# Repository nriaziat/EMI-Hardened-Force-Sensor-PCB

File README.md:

# EMI Hardened Force Sensor PCB

<!--- This template should be used if the project contains hardware designs. If the project contains both hardware and software designs, please also refer to software-readme-template.md and incorporate relevant sections. -->

## Contents

<!---List file contents of the project, in table.--->

| File/folder | Description |
|-------------|-------------|
| `MazeStrainGaugeAmplifier.pdf`       | Schematic |
| `ibom.html`       | Bill of materials |
| `PCB.pdf`        | Report on PCB stack-up |
| `README.md` | This README file. |
| `LICENSE`   | The license for the project. |

## Design Tools

* KiCAD 6.0

## Key concepts

For more information about this project, please refer to our publication: [Riaziat, Naveed D., et al. "Investigating Haptic Feedback in Vision-Deficient Millirobot Telemanipulation." IEEE Robotics and Automation Letters (2024)](https://ieeexplore.ieee.org/abstract/document/10521760/).
Designed for use with the Texas Measurment [QMFLA-5-350-11-1LJAY-F](https://tml.jp/e/product/strain_gauge/mf_list.html) and the [RP2040](https://www.raspberrypi.com/products/rp2040/).
For maximum EMI resistance, we reccommend using twisted and shielded cabling as well as the included 3D printed housing with copper tape lining. 

## Project expectations

* The design has been manufactured and tested. Board was ordered through OSH Park and hand assembled.

### Expected support for the project

<!---If you will reply to issues, please suggest how users should report problems or reach out. Github issues is preferable.--->

* Will attempt reply to Github Issues with no guarantee.
* Project is provided without any support. 

## License

For details on license, see LICENSE in this directory.

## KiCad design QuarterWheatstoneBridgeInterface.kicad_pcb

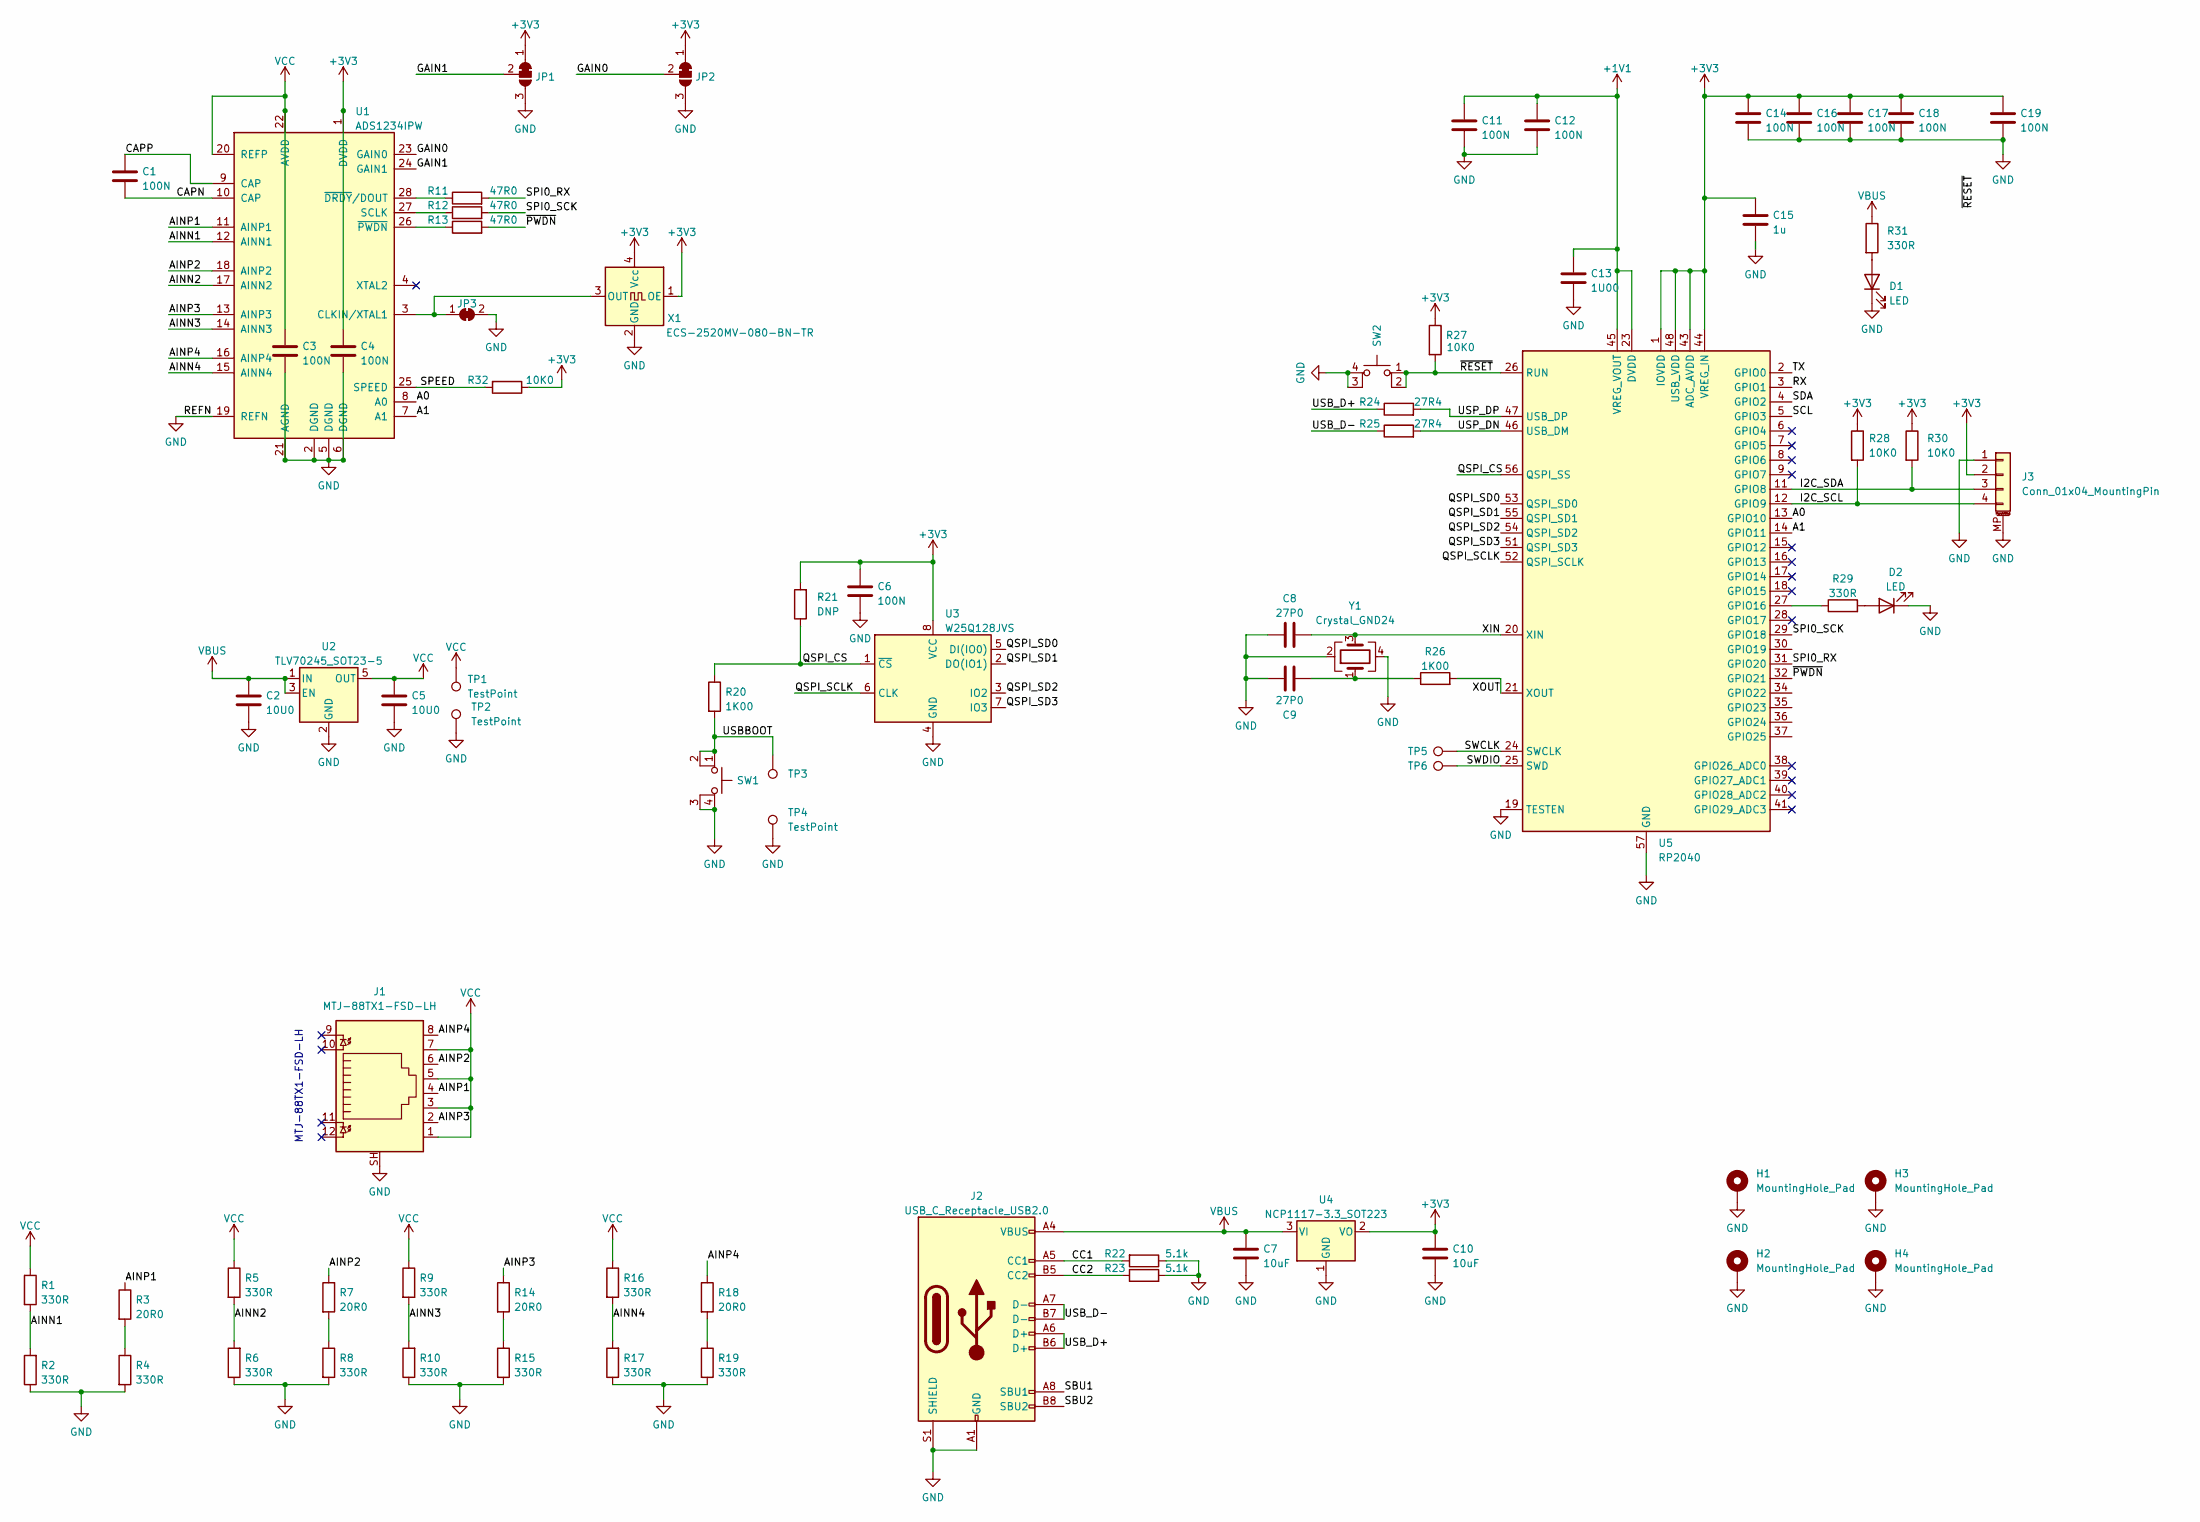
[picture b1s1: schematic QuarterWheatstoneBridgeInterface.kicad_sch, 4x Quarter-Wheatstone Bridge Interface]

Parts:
C1, C3, C4, C6, C11, C12, C14, C16, C17, C18, C19: 100N; C_0402_1005Metric_Pad0.74x0.62mm_HandSolder
C2, C5: 10U0; C_0402_1005Metric_Pad0.74x0.62mm_HandSolder
C7, C10: 10uF; C_0402_1005Metric_Pad0.74x0.62mm_HandSolder
C8, C9: 27P0; C_0402_1005Metric_Pad0.74x0.62mm_HandSolder
C13: 1U00; C_0402_1005Metric_Pad0.74x0.62mm_HandSolder
C15: 1u; C_0402_1005Metric_Pad0.74x0.62mm_HandSolder
D1, D2: LED; LED_0603_1608Metric_Pad1.05x0.95mm_HandSolder
H1, H2, H3, H4: MountingHole_Pad; MountingHole_2.2mm_M2_DIN965_Pad
J1: MTJ-88TX1-FSD-LH; RJ45_Hanrun_HR911105A
J2: USB_C_Receptacle_USB2.0; USB_C_Receptacle_HRO_TYPE-C-31-M-12
J3: Conn_01x04_MountingPin; JST_SH_BM04B-SRSS-TB_1x04-1MP_P1.00mm_Vertical
JP1, JP2: SolderJumper_3_Bridged12; SolderJumper-3_P1.3mm_Bridged12_Pad1.0x1.5mm
JP3: SolderJumper_2_Bridged; SolderJumper-2_P1.3mm_Bridged_Pad1.0x1.5mm
R1, R2, R4, R5, R6, R8, R9, R10, R15, R16, R17, R19, R29, R31: 330R; R_0402_1005Metric_Pad0.72x0.64mm_HandSolder
R3, R7, R14, R18: 20R0; R_0402_1005Metric_Pad0.72x0.64mm_HandSolder
R11, R12, R13: 47R0; R_0402_1005Metric_Pad0.72x0.64mm_HandSolder
R20, R26: 1K00; R_0402_1005Metric_Pad0.72x0.64mm_HandSolder
R21: DNP; R_0402_1005Metric_Pad0.72x0.64mm_HandSolder
R22, R23: 5.1k; R_0402_1005Metric_Pad0.72x0.64mm_HandSolder
R24, R25: 27R4; R_0402_1005Metric_Pad0.72x0.64mm_HandSolder
R27, R28, R30, R32: 10K0; R_0402_1005Metric_Pad0.72x0.64mm_HandSolder
SW1, SW2: SW_MEC_5E; SW_TH_Tactile_Omron_B3F-10xx
TP1, TP2, TP4: TestPoint; TestPoint_Pad_D3.0mm
TP3, TP5, TP6: TestPoint; TestPoint_Pad_D4.0mm
U1: ADS1234IPW; TSSOP-28_4.4x9.7mm_P0.65mm
U2: TLV70245_SOT23-5; SOT-23-5
U3: W25Q128JVS; SOIC-8_5.23x5.23mm_P1.27mm
U4: NCP1117-3.3_SOT223; SOT-223-3_TabPin2
U5: RP2040; QFN-56-1EP_7x7mm_P0.4mm_EP3.2x3.2mm
X1: ECS-2520MV-080-BN-TR; Oscillator_SMD_SeikoEpson_SG210-4Pin_2.5x2.0mm
Y1: Crystal_GND24; Crystal_SMD_3225-4Pin_3.2x2.5mm_HandSoldering

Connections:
+1V1: C11.1, C12.1, C13.1, U5.23 (DVDD), U5.45 (VREG_VOUT), U5.50 (DVDD)
+3V3: C4.1, C6.1, C10.1, C14.1, C15.1, C16.1, C17.1, C18.1, C19.1, J3.2, JP1.1 (A), JP2.1 (A), R21.2, R27.1, R28.1, R30.1, R32.1, U1.1 (DVDD), U3.8 (VCC), U4.2 (VO), U5.1 (IOVDD), U5.10 (IOVDD), U5.22 (IOVDD), U5.33 (IOVDD), U5.42 (IOVDD), U5.43 (ADC_AVDD), U5.44 (VREG_IN), U5.48 (USB_VDD), U5.49 (IOVDD), X1.1 (OE), X1.4 (Vcc)
/A0: U1.8 (A0), U5.13 (GPIO10)
/A1: U1.7 (A1), U5.14 (GPIO11)
/AINN1: R1.2, R2.2, U1.12 (AINN1)
/AINN2: R5.2, R6.2, U1.17 (AINN2)
/AINN3: R9.2, R10.2, U1.14 (AINN3)
/AINN4: R16.2, R17.2, U1.15 (AINN4)
/AINP1: J1.4, R3.1, U1.11 (AINP1)
/AINP2: J1.6, R7.1, U1.18 (AINP2)
/AINP3: J1.2, R14.1, U1.13 (AINP3)
/AINP4: J1.8, R18.1, U1.16 (AINP4)
/CAPN: C1.2, U1.10 (CAP)
/CAPP: C1.1, U1.9 (CAP)
/CC1: J2.A5 (CC1), R22.2
/CC2: J2.B5 (CC2), R23.1
/GAIN0: JP2.2 (C), U1.23 (GAIN0)
/GAIN1: JP1.2 (C), U1.24 (GAIN1)
/I2C_SCL: J3.4, R28.2, U5.12 (GPIO9)
/I2C_SDA: J3.3, R30.2, U5.11 (GPIO8)
/QSPI_CS: R20.1, R21.1, U3.1 (~CS), U5.56 (QSPI_SS)
/QSPI_SCLK: U3.6 (CLK), U5.52 (QSPI_SCLK)
/QSPI_SD0: U3.5 (DI(IO0)), U5.53 (QSPI_SD0)
/QSPI_SD1: U3.2 (DO(IO1)), U5.55 (QSPI_SD1)
/QSPI_SD2: U3.3 (IO2), U5.54 (QSPI_SD2)
/QSPI_SD3: U3.7 (IO3), U5.51 (QSPI_SD3)
/RX: U5.3 (GPIO1)
/SBU1: J2.A8 (SBU1)
/SBU2: J2.B8 (SBU2)
/SCL: U5.5 (GPIO3)
/SDA: U5.4 (GPIO2)
/SPEED: R32.2, U1.25 (SPEED)
/SPI0_RX: R11.2, U5.31 (GPIO20)
/SPI0_SCK: R12.2, U5.29 (GPIO18)
/SWCLK: TP5.1, U5.24 (SWCLK)
/SWDIO: TP6.1, U5.25 (SWD)
/TX: U5.2 (GPIO0)
/USBBOOT: R20.2, SW1.1, SW1.2, TP3.1
/USB_D+: J2.A6 (D+), J2.B6 (D+), R24.1
/USB_D-: J2.A7 (D-), J2.B7 (D-), R25.1
/USP_DN: R25.2, U5.46 (USB_DM)
/USP_DP: R24.2, U5.47 (USB_DP)
/XIN: C8.2, U5.20 (XIN), Y1.3
/XOUT: R26.2, U5.21 (XOUT)
/~PWDN: R13.2, U5.32 (GPIO21)
/~RESET: R27.2, SW2.1, SW2.2, U5.26 (RUN)
GND: C2.2, C3.2, C4.2, C5.2, C6.2, C7.2, C8.1, C9.2, C10.2, C11.2, C12.2, C13.2, C14.2, C15.2, C16.2, C17.2, C18.2, C19.2, D1.1 (K), D2.1 (K), H1.1, H2.1, H3.1, H4.1, J1.SH, J2.A1 (GND), J2.A12 (GND), J2.B1 (GND), J2.B12 (GND), J2.S1 (SHIELD), J3.1, J3.MP (MountPin), JP1.3 (B), JP2.3 (B), JP3.2 (B), R2.1, R4.2, R6.1, R8.2, R10.1, R15.2, R17.1, R19.2, R22.1, R23.2, SW1.3 (K), SW1.4 (A), SW2.3 (K), SW2.4 (A), TP2.1, TP4.1, U1.2 (DGND), U1.5 (DGND), U1.6 (DGND), U1.19 (REFN), U1.21 (AGND), U2.2 (GND), U3.4 (GND), U4.1 (GND), U5.19 (TESTEN), U5.57 (GND), X1.2 (GND), Y1.2, Y1.4
unnamed: C9.1, R26.1, Y1.1
unnamed: D1.2 (A), R31.2
unnamed: D2.2 (A), R29.2
unnamed: JP3.1 (A), U1.3 (CLKIN/XTAL1), X1.3 (OUT)
unnamed: R3.2, R4.1
unnamed: R7.2, R8.1
unnamed: R11.1, U1.28 (~DRDY/DOUT)
unnamed: R12.1, U1.27 (SCLK)
unnamed: R13.1, U1.26 (~PWDN)
unnamed: R14.2, R15.1
unnamed: R18.2, R19.1
unnamed: R29.1, U5.27 (GPIO16)
VBUS: C2.1, C7.1, J2.A4 (VBUS), J2.A9 (VBUS), J2.B4 (VBUS), J2.B9 (VBUS), R31.1, U2.1 (IN), U2.3 (EN), U4.3 (VI)
VCC: C3.1, C5.1, J1.1, J1.3, J1.5, J1.7, R1.1, R5.1, R9.1, R16.1, TP1.1, U1.20 (REFP), U1.22 (AVDD), U2.5 (OUT)

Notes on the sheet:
MTJ-88TX1-FSD-LH

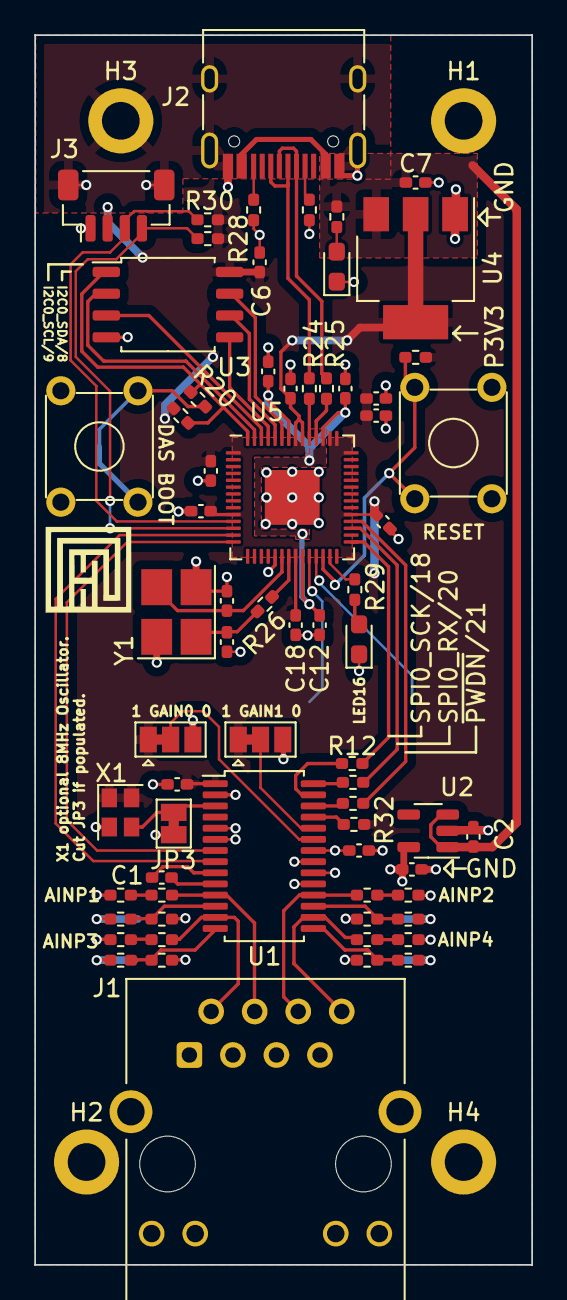
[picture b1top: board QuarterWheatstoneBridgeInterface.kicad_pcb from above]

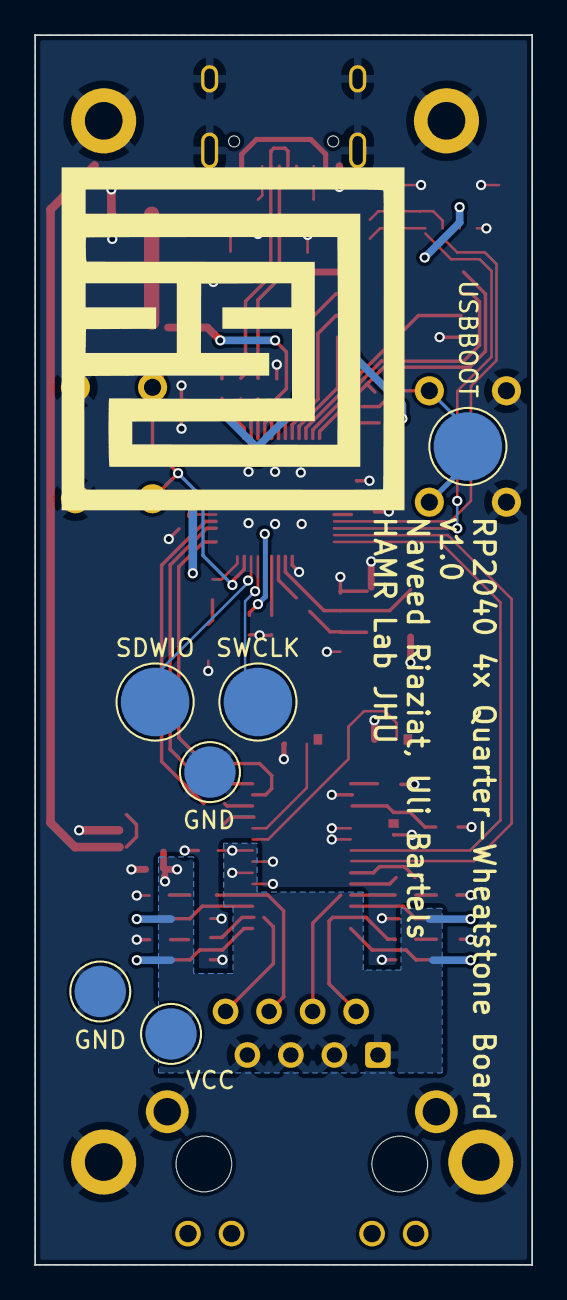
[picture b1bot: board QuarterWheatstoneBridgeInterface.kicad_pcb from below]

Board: 2 copper layers, 29.0 x 71.8 mm, 78 parts (6 on the bottom side), 55 nets.

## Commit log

2023-10-10 Create LICENSE
2023-10-10 initial push
2023-10-10 add bom
2023-10-10 Update README.md template
2023-10-16 add housing
2023-10-16 add universal STL files
2023-10-16 Update README.md with image
2023-10-16 Update README.md with links and added info
2024-11-08 Update README.md
    Adding link to publication/addressing TODO. :-)
